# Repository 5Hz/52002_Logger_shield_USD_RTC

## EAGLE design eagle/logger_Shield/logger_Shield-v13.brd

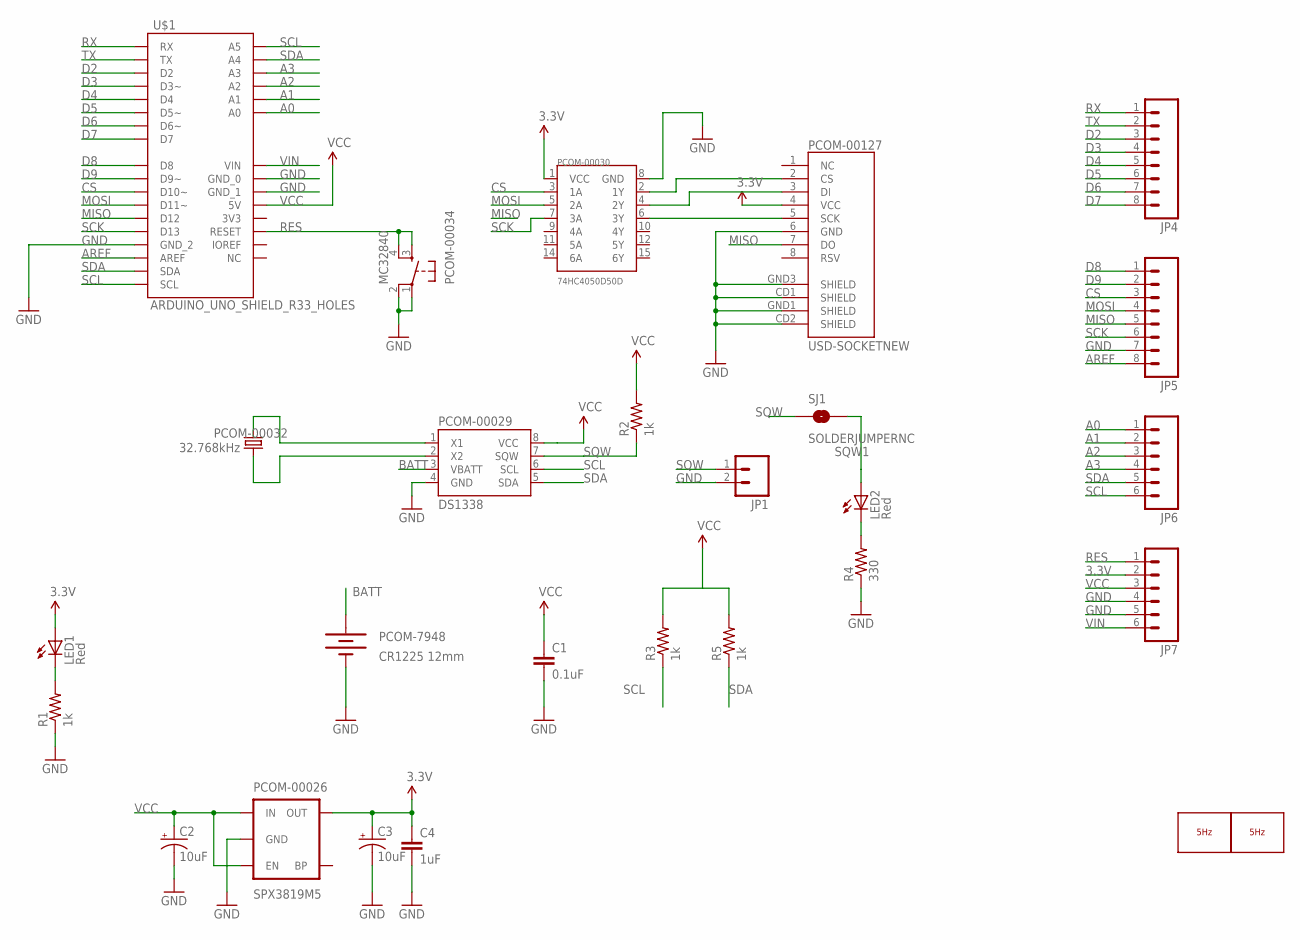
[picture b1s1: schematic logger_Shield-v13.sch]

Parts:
C1: 0.1uF; 0603-CAP
C2, C3: 10uF; EIA3216
C4: 1uF; 0603-CAP
JP1: M02PTH; 1X02
JP4, JP5: M08; 1X08
JP6, JP7: M06SIP; 1X06
LED1, LED2: Red; LED-0603
LOGO1: LOGO_5HZ_H_COOPER_15MM; 5HZ_LOGO_H_COOPER_15MM
LOGO2: LOGO_5HZ_MAIN_10MM; 5HZ_LOGO_MAIN_10MM
PCOM-00026: SPX3819M5; SOT23-5
PCOM-00029: DS1338; SO08
PCOM-00030: 74HC4050D50D; SO016
PCOM-00032: 32.768kHz; CRYSTAL-32KHZ-SMD
PCOM-00034: MC32840; TACTILE_SWITCH_SMD
PCOM-00127: USD-SOCKETNEW; MICRO-SD-SOCKET-PP
PCOM-7948: CR1225 12mm; BATTCON_12MM_PTH
R1, R2, R3, R5: 1k; 0603-RES
R4: 330; 0603-RES
SJ1: SOLDERJUMPERNC; SJ_2S
U$1: ARDUINO_UNO_SHIELD_R33_HOLES; UNO_R3_SHIELD_3_HOLES_NO_SILK

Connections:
3.3V: C3.A (+), C4.1, JP7.2, LED1.A, PCOM-00026.5 (OUT), PCOM-00030.1 (VCC), PCOM-00127.4 (VCC)
A0: JP6.1, U$1.A0
A1: JP6.2, U$1.A1
A2: JP6.3, U$1.A2
A3: JP6.4, U$1.A3
AREF: JP5.8, U$1.AREF
BATT: PCOM-00029.3 (VBATT), PCOM-7948.VCC@1 (+)
CS: JP5.3, PCOM-00030.3 (1A), U$1.D10 (D10~)
D2: JP4.3, U$1.D2
D3: JP4.4, U$1.D3 (D3~)
D4: JP4.5, U$1.D4
D5: JP4.6, U$1.D5 (D5~)
D6: JP4.7, U$1.D6 (D6~)
D7: JP4.8, U$1.D7
D8: JP5.1, U$1.D8
D9: JP5.2, U$1.D9 (D9~)
GND: C1.2, C2.C (-), C3.C (-), C4.2, JP1.2, JP5.7, JP7.4, JP7.5, PCOM-00026.2 (GND), PCOM-00029.4 (GND), PCOM-00030.8 (GND), PCOM-00034.1, PCOM-00034.2, PCOM-00127.6 (GND), PCOM-00127.CD1 (SHIELD), PCOM-00127.CD2 (SHIELD), PCOM-00127.GND1 (SHIELD), PCOM-00127.GND3 (SHIELD), PCOM-7948.GND (-), R1.1, R4.1, U$1.GND_0, U$1.GND_1, U$1.GND_2
MISO: JP5.5, PCOM-00127.7 (DO), U$1.D12
MOSI: JP5.4, PCOM-00030.5 (2A), U$1.D11 (D11~)
unnamed: PCOM-00029.1 (X1), PCOM-00032.X2 (2)
unnamed: PCOM-00030.4 (2Y), PCOM-00127.3 (DI)
unnamed: PCOM-00030.6 (3Y), PCOM-00127.5 (SCK)
unnamed: LED1.C, R1.2
unnamed: PCOM-00029.2 (X2), PCOM-00032.X1 (1)
unnamed: LED2.C, R4.2
unnamed: PCOM-00030.2 (1Y), PCOM-00127.2 (CS)
RES: JP7.1, PCOM-00034.3, PCOM-00034.4, U$1.RES (RESET)
RX: JP4.1, U$1.RX
SCK: JP5.6, PCOM-00030.7 (3A), U$1.D13
SCL: JP6.6, PCOM-00029.6 (SCL), R3.1, U$1.A5, U$1.SCL
SDA: JP6.5, PCOM-00029.5 (SDA), R5.1, U$1.A4, U$1.SDA
SQW: JP1.1, PCOM-00029.7 (SQW), R2.1, SJ1.1
SQW1: LED2.A, SJ1.2
TX: JP4.2, U$1.TX
VCC: C1.1, C2.A (+), JP7.3, PCOM-00026.1 (IN), PCOM-00026.3 (EN), PCOM-00029.8 (VCC), R2.2, R3.2, R5.2, U$1.5V
VIN: JP7.6, U$1.VIN

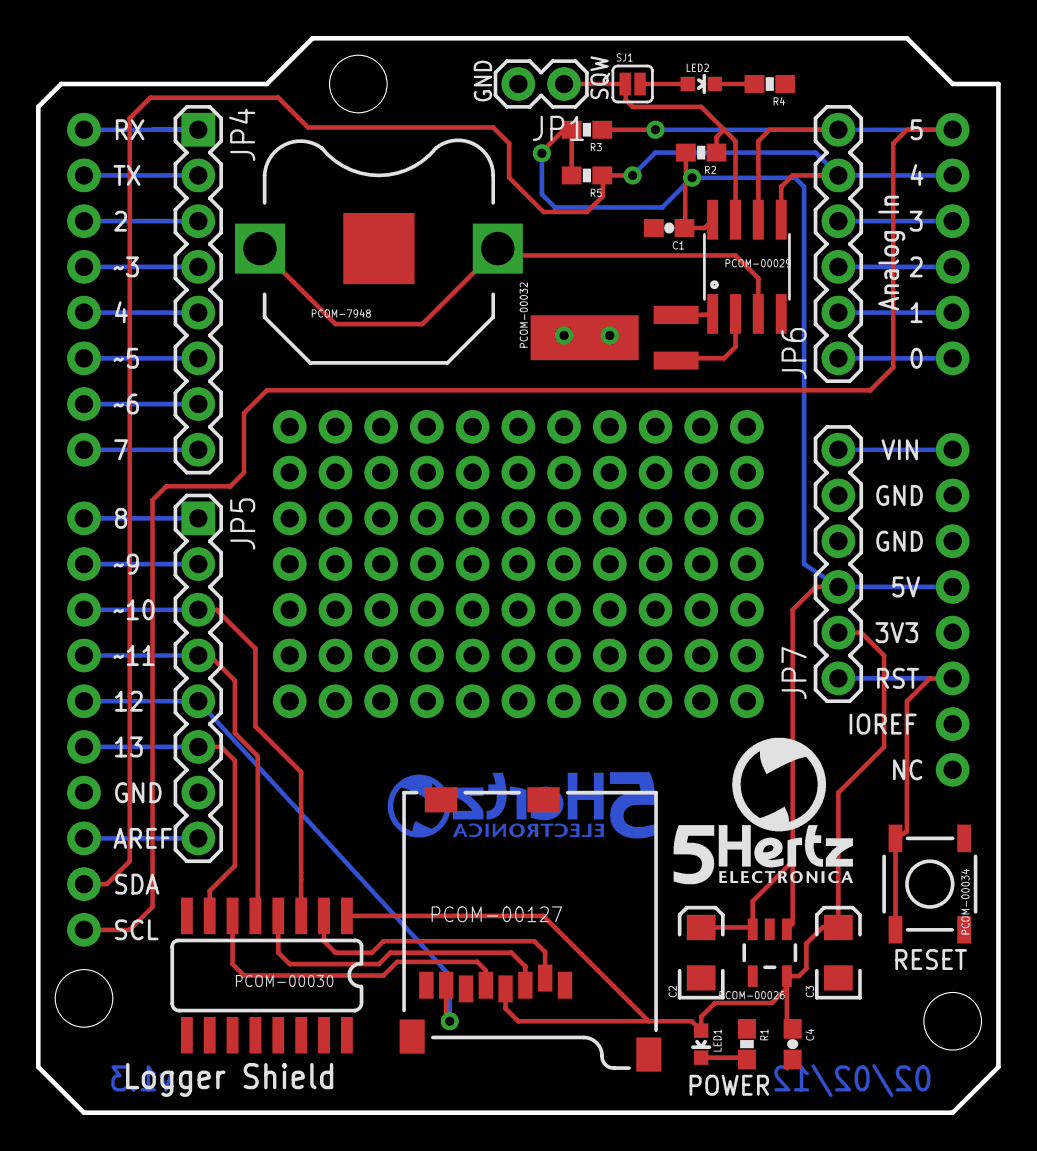
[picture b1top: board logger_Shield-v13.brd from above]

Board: 2 copper layers, 53.3 x 59.7 mm, 27 parts (1 on the bottom side), 36 nets.

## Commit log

2014-01-09 creación
